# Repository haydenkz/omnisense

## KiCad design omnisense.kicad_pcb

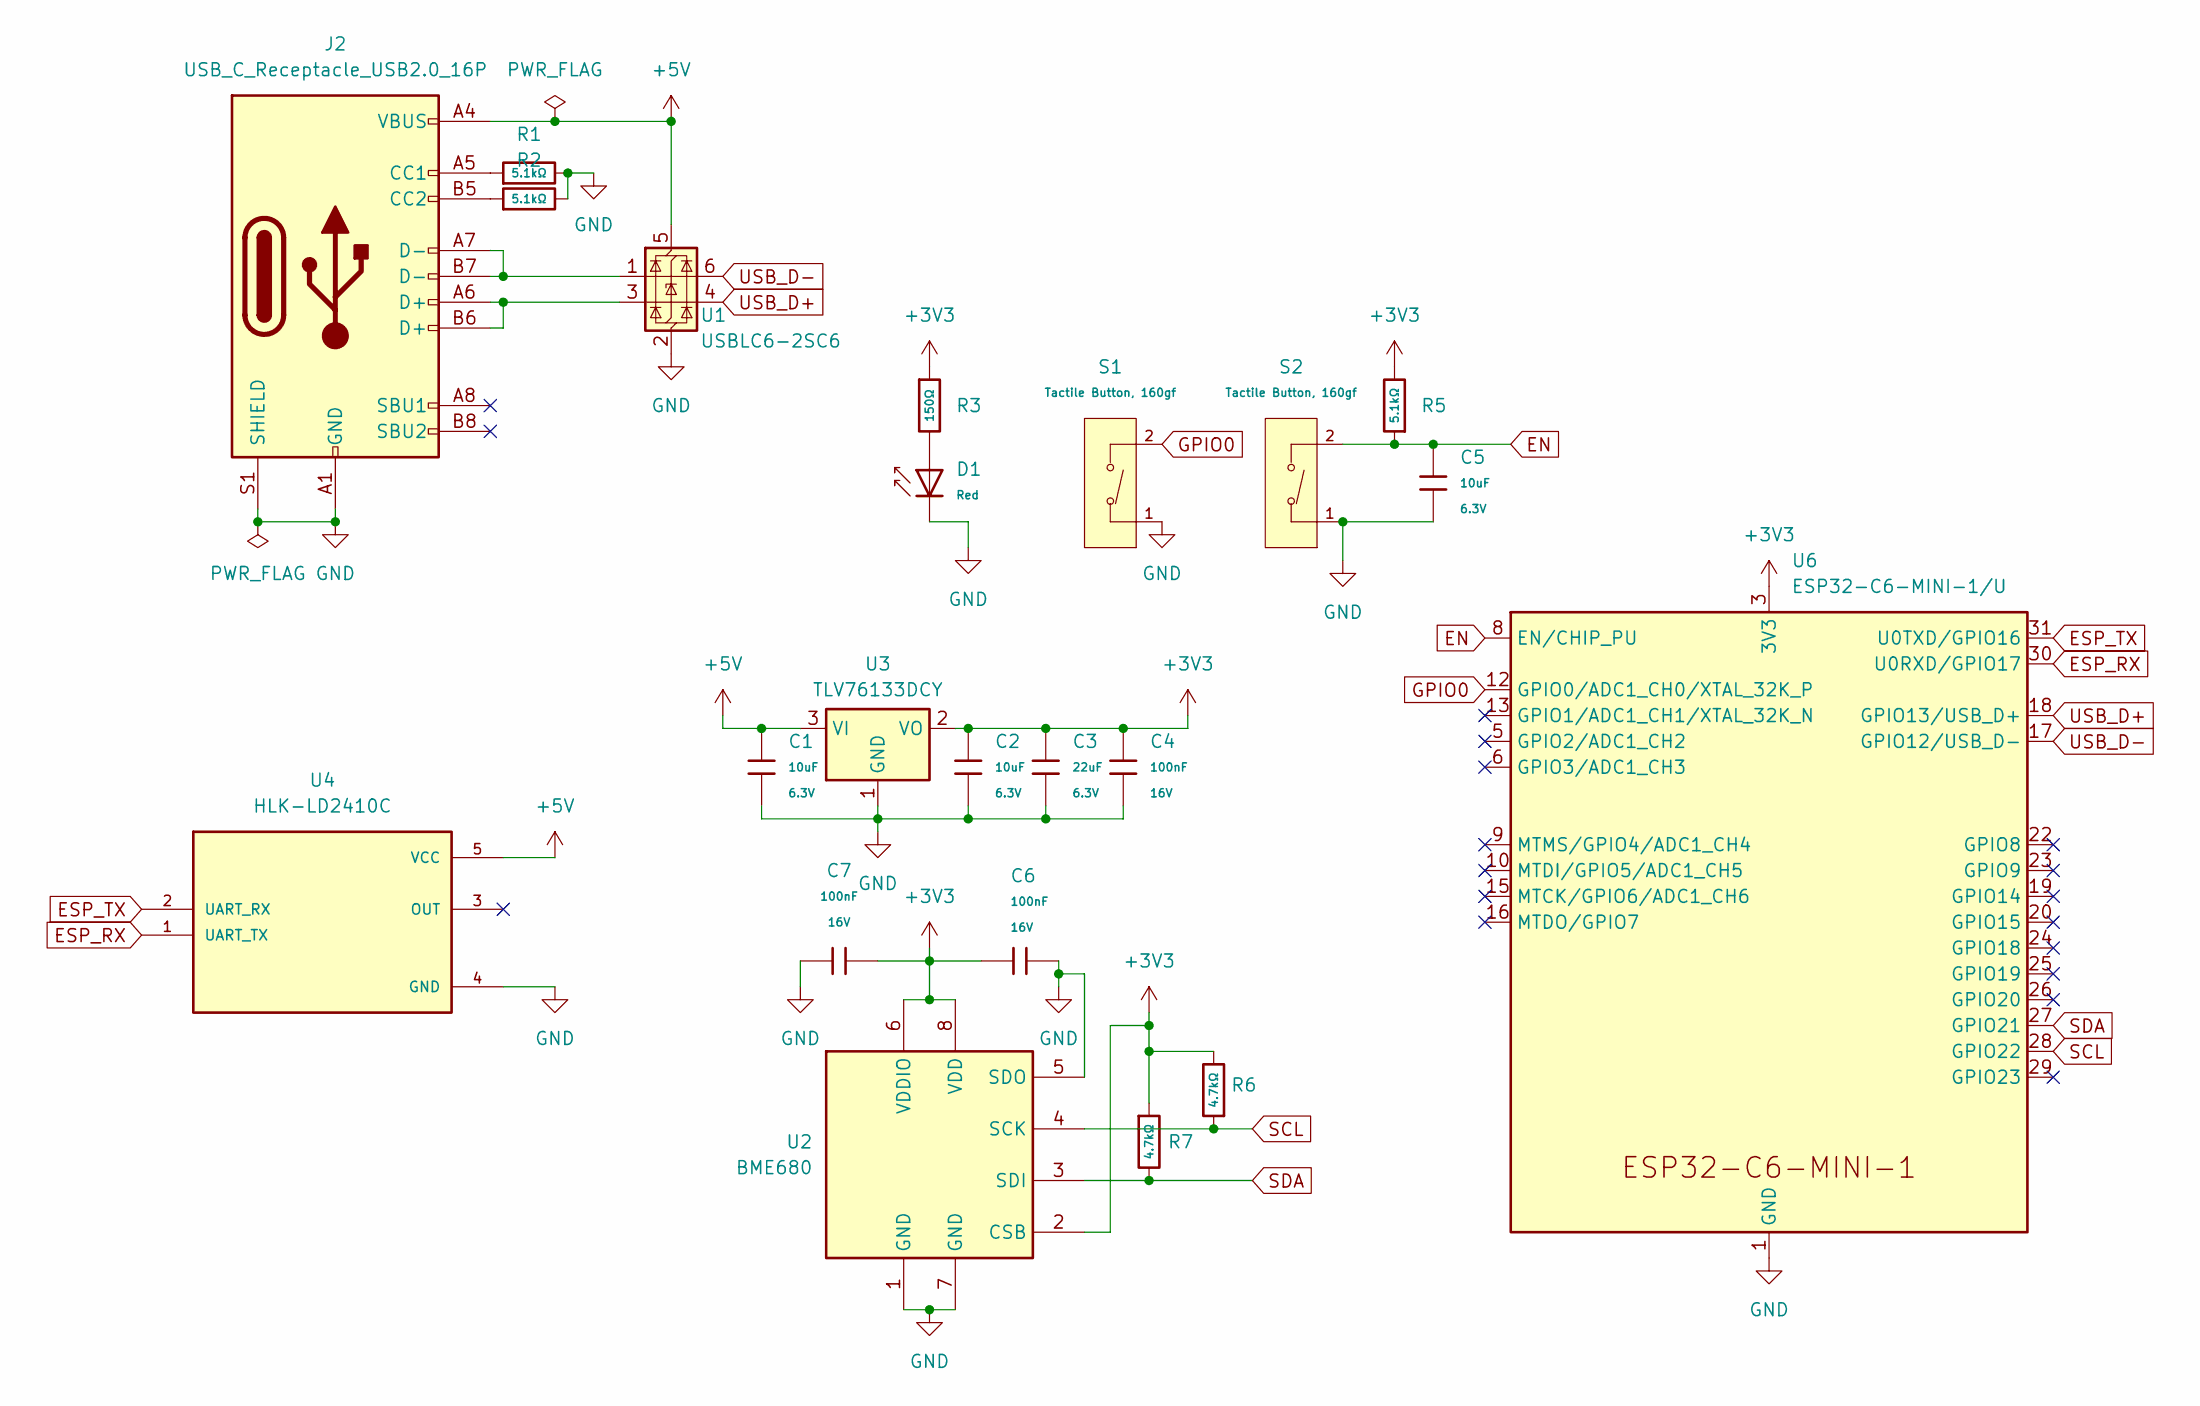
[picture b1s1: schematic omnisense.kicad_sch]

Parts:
C1, C2, C5: 10uF; C_0402; Voltage Rated 6.3V; Tolerance ±20%; Part CL05A106MQ5NUNC; LCSC C15525
C3: 22uF; C_0603; Voltage Rated 6.3V; Tolerance ±20%; Part CL10A226MQ8NRNC; LCSC C59461
C4, C6, C7: 100nF; C_0402; Voltage Rated 16V; Tolerance ±10%; Part CL05B104KO5NNNC; LCSC C1525
D1: Red; D_0603; Part KT-0603R; LCSC C2286
J2: USB_C_Receptacle_USB2.0_16P; USB_C_Receptacle_HRO_TYPE-C-31-M-12
R1, R2, R5: 5.1kΩ; R_0402; Overload Voltage (Max) 50V; Tolerance ±1%; Part 0402WGF5101TCE; LCSC C25905
R3: 150Ω; R_0402; Overload Voltage (Max) 50V; Tolerance ±1%; Part 0402WGF1500TCE; LCSC C25082
R6, R7: 4.7kΩ; R_0402; Overload Voltage (Max) 50V; Tolerance ±1%; Part 0402WGF4701TCE; LCSC C25900
S1, S2: Tactile Button, 160gf; SW_TS-1088-AR02016; Voltage Rating (Dc) 12V; Part TS-1088-AR02016; LCSC C720477
U1: USBLC6-2SC6; SOT-23-6
U2: BME680; Bosch_LGA-8_3x3mm_P0.8mm_ClockwisePinNumbering
U3: TLV76133DCY; SOT-223-3_TabPin2
U4: HLK-LD2410C; MODULE_HLK-LD2410C
U6: ESP32-C6-MINI-1/U; ESP32-C6-MINI-1

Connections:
+3V3: C2.1, C3.1, C4.1, C6.1, C7.1, R3.1, R5.2, R6.2, R7.1, U2.2 (CSB), U2.6 (VDDIO), U2.8 (VDD), U3.2 (VO), U6.3 (3V3)
+5V: C1.1, J2.A4 (VBUS), J2.A9 (VBUS), J2.B4 (VBUS), J2.B9 (VBUS), U1.5 (VBUS), U3.3 (VI), U4.5 (VCC)
EN: C5.1, R5.1, S2.2 (B), U6.8 (EN/CHIP_PU)
ESP_RX: U4.1 (UART_TX), U6.30 (U0RXD/GPIO17)
ESP_TX: U4.2 (UART_RX), U6.31 (U0TXD/GPIO16)
GND: C1.2, C2.2, C3.2, C4.2, C5.2, C6.2, C7.2, D1.1, J2.A1 (GND), J2.A12 (GND), J2.B1 (GND), J2.B12 (GND), J2.S1 (SHIELD), R1.2, R2.2, S1.1 (A), S2.1 (A), U1.2 (GND), U2.1 (GND), U2.5 (SDO), U2.7 (GND), U3.1 (GND), U4.4 (GND), U6.1 (GND), U6.2 (GND), U6.11 (GND), U6.14 (GND), U6.36 (GND), U6.37 (GND), U6.38 (GND), U6.39 (GND), U6.40 (GND), U6.41 (GND), U6.42 (GND), U6.43 (GND), U6.44 (GND), U6.45 (GND), U6.46 (GND), U6.47 (GND), U6.48 (GND), U6.49 (GND), U6.50 (GND), U6.51 (GND), U6.52 (GND), U6.53 (GND)
GPIO0: S1.2 (B), U6.12 (GPIO0/ADC1_CH0/XTAL_32K_P)
unnamed: D1.2, R3.2
unnamed: J2.A5 (CC1), R1.1
unnamed: J2.B5 (CC2), R2.1
unnamed: J2.A6 (D+), J2.B6 (D+), U1.3 (I/O2)
unnamed: J2.A7 (D-), J2.B7 (D-), U1.1 (I/O1)
SCL: R6.1, U2.4 (SCK), U6.28 (GPIO22)
SDA: R7.2, U2.3 (SDI), U6.27 (GPIO21)
USB_D+: U1.4 (I/O2), U6.18 (GPIO13/USB_D+)
USB_D-: U1.6 (I/O1), U6.17 (GPIO12/USB_D-)

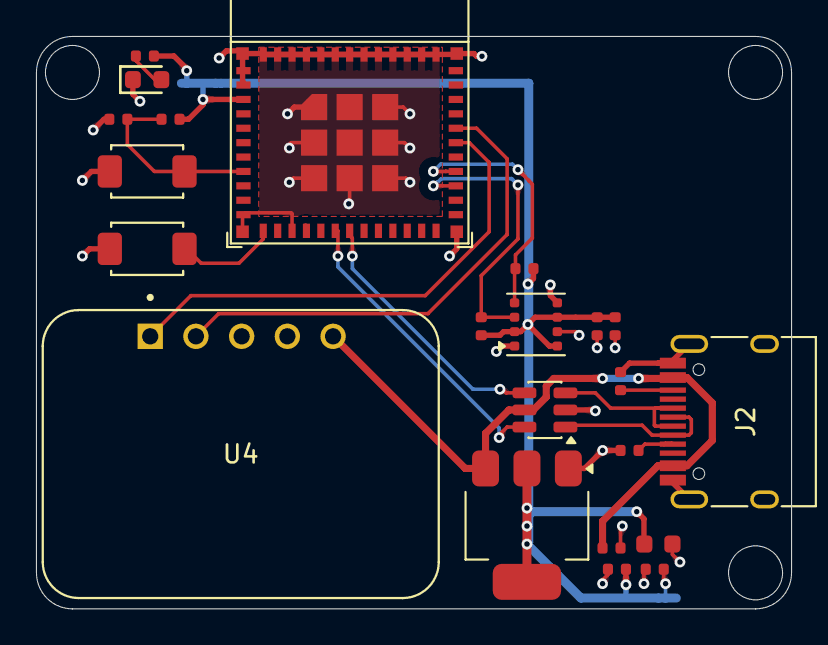
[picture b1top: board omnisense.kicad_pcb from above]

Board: 4 copper layers, 42.0 x 31.8 mm, 22 parts (0 on the bottom side), 16 nets.

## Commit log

2026-03-11 init
2026-03-13 lgtm
